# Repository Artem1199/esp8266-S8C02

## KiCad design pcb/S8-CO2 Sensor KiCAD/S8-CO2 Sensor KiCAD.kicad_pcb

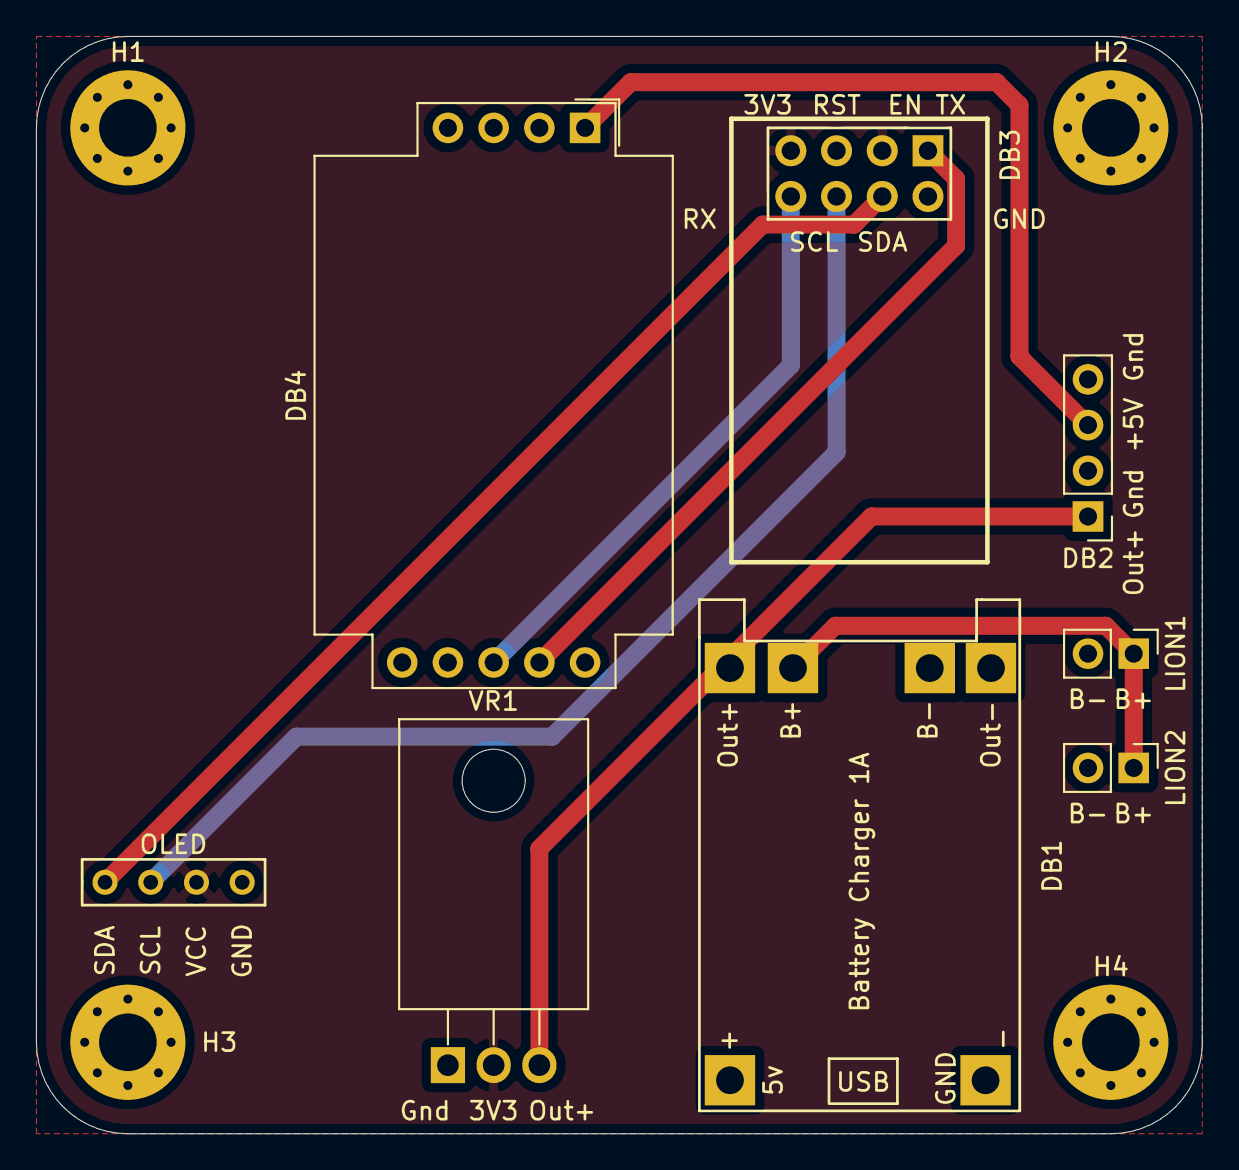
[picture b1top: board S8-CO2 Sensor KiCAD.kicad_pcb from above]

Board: 2 copper layers, 64.8 x 61.0 mm, 12 parts (0 on the bottom side), 9 nets.

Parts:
DB1: 03962A; TP4056-18650
DB2: XL6019; PinHeader_1x04_P2.54mm_Vertical
DB3: ESP-01v090; ESP-01
DB4: 004-0-0053; Senseair_S8_Up
DS1: SSD1306BOB; OLED
H1, H2, H3, H4: MountingHole_Pad; MountingHole_3.2mm_M3_Pad_Via
LION1, LION2: 3.7V BAT; PinHeader_1x02_P2.54mm_Vertical
VR1: MC33269; TO-220F-3_Horizontal_TabDown

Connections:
+3V3: DB3.3, DB3.7, DS1.3, VR1.2
+5V: DB2.3, DB4.1
/SCL: DB3.6, DS1.2
/SDA: DB3.4, DS1.1
GND: DB1.2, DB1.4, DB1.6, DB2.2, DB2.4, DB3.2, DB4.2, DS1.4, H1.1, H2.1, H3.1, H4.1, LION1.2, LION2.2, VR1.1
unnamed: DB1.3, DB2.1, VR1.3
unnamed: DB1.5, LION1.1, LION2.1
unnamed: DB3.1, DB4.8
unnamed: DB3.8, DB4.7

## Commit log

2022-04-03 added gitignore
2022-04-03 Added pushover comms
2022-04-11 Working, spams pushover with CO2 values
2022-04-17 Added KiCAD files, latest code with working SW - no LCD
2022-04-20 adding 3d models
